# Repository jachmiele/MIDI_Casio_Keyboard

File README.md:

# MIDI Casio Keyboard
The goal of this project was to convert an old Casio keyboard into a MIDI controller.<br><br>
<h4>Requirements</h4>
MIDI.h library is required to run this code https://github.com/FortySevenEffects/arduino_midi_library/

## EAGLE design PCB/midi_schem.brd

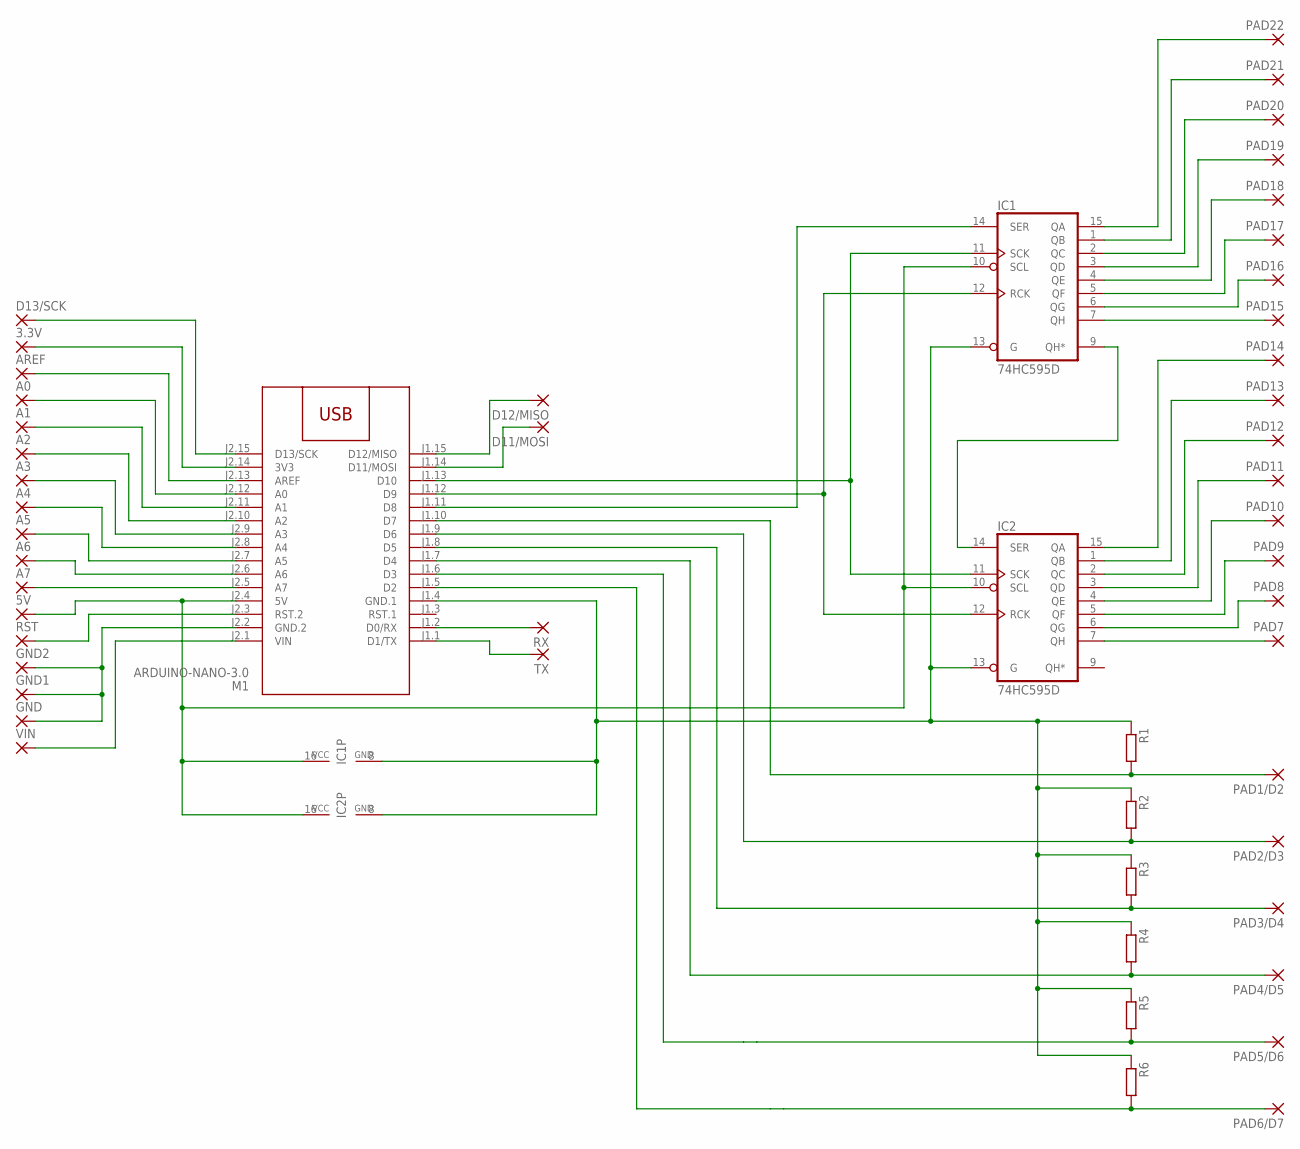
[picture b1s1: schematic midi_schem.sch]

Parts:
3.3V, 5V: 2,54/0,8
A0, A1, A2, A3, A4, A5, A6, A7: 2,54/0,8
AREF: 2,54/0,8
D11/MOSI, D12/MISO, D13/SCK: 2,54/0,8
GND, GND1, GND2: 2,54/0,8
IC1, IC2: 74HC595D; SO16
M1: ARDUINO-NANO-3.0
PAD1/D2, PAD2/D3, PAD3/D4, PAD4/D5, PAD5/D6, PAD6/D7, PAD7, PAD8, PAD9, PAD10, PAD11, PAD12, PAD13, PAD14, PAD15, PAD16, PAD17, PAD18, PAD19, PAD20, PAD21, PAD22: SMD2; SMD1,27-2,54
R1, R2, R3, R4, R5, R6: R-EU_0207/10; 0207/10
RST: 2,54/0,8
RX: 2,54/0,8
TX: 2,54/0,8
VIN: 2,54/0,8

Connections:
unnamed: IC1.14 (SER), M1.J1.11 (D8)
unnamed: 5V.1, IC1.10 (SCL), IC1.16 (VCC), IC2.10 (SCL), IC2.16 (VCC), M1.J2.4 (5V)
unnamed: IC1.8 (GND), IC1.13 (G), IC2.8 (GND), IC2.13 (G), M1.J1.4 (GND.1), R1.1, R2.1, R3.1, R4.1, R5.1, R6.1
unnamed: IC1.7 (QH), PAD15.1
unnamed: IC1.6 (QG), PAD16.1
unnamed: IC1.5 (QF), PAD17.1
unnamed: IC1.4 (QE), PAD18.1
unnamed: IC1.3 (QD), PAD19.1
unnamed: IC1.2 (QC), PAD20.1
unnamed: IC1.1 (QB), PAD21.1
unnamed: IC1.15 (QA), PAD22.1
unnamed: IC2.7 (QH), PAD7.1
unnamed: IC2.6 (QG), PAD8.1
unnamed: IC2.5 (QF), PAD9.1
unnamed: IC2.4 (QE), PAD10.1
unnamed: IC2.3 (QD), PAD11.1
unnamed: IC2.2 (QC), PAD12.1
unnamed: IC2.1 (QB), PAD13.1
unnamed: IC2.15 (QA), PAD14.1
unnamed: IC1.12 (RCK), IC2.12 (RCK), M1.J1.12 (D9)
unnamed: IC1.11 (SCK), IC2.11 (SCK), M1.J1.13 (D10)
unnamed: IC1.9 (QH*), IC2.14 (SER)
unnamed: A7.1, M1.J2.5 (A7)
unnamed: A6.1, M1.J2.6 (A6)
unnamed: A5.1, M1.J2.7 (A5)
unnamed: A4.1, M1.J2.8 (A4)
unnamed: A3.1, M1.J2.9 (A3)
unnamed: A2.1, M1.J2.10 (A2)
unnamed: A1.1, M1.J2.11 (A1)
unnamed: A0.1, M1.J2.12 (A0)
unnamed: AREF.1, M1.J2.13 (AREF)
unnamed: 3.3V.1, M1.J2.14 (3V3)
unnamed: D13/SCK.1, M1.J2.15 (D13/SCK)
unnamed: M1.J1.10 (D7), PAD1/D2.1, R1.2
unnamed: M1.J1.2 (D0/RX), RX.1
unnamed: M1.J1.1 (D1/TX), TX.1
unnamed: D11/MOSI.1, M1.J1.14 (D11/MOSI)
unnamed: D12/MISO.1, M1.J1.15 (D12/MISO)
unnamed: M1.J2.3 (RST.2), RST.1
unnamed: GND.1, GND1.1, GND2.1, M1.J2.2 (GND.2)
unnamed: M1.J2.1 (VIN), VIN.1
unnamed: M1.J1.9 (D6), PAD2/D3.1, R2.2
unnamed: M1.J1.8 (D5), PAD3/D4.1, R3.2
unnamed: M1.J1.7 (D4), PAD4/D5.1, R4.2
unnamed: M1.J1.6 (D3), PAD5/D6.1, R5.2
unnamed: M1.J1.5 (D2), PAD6/D7.1, R6.2

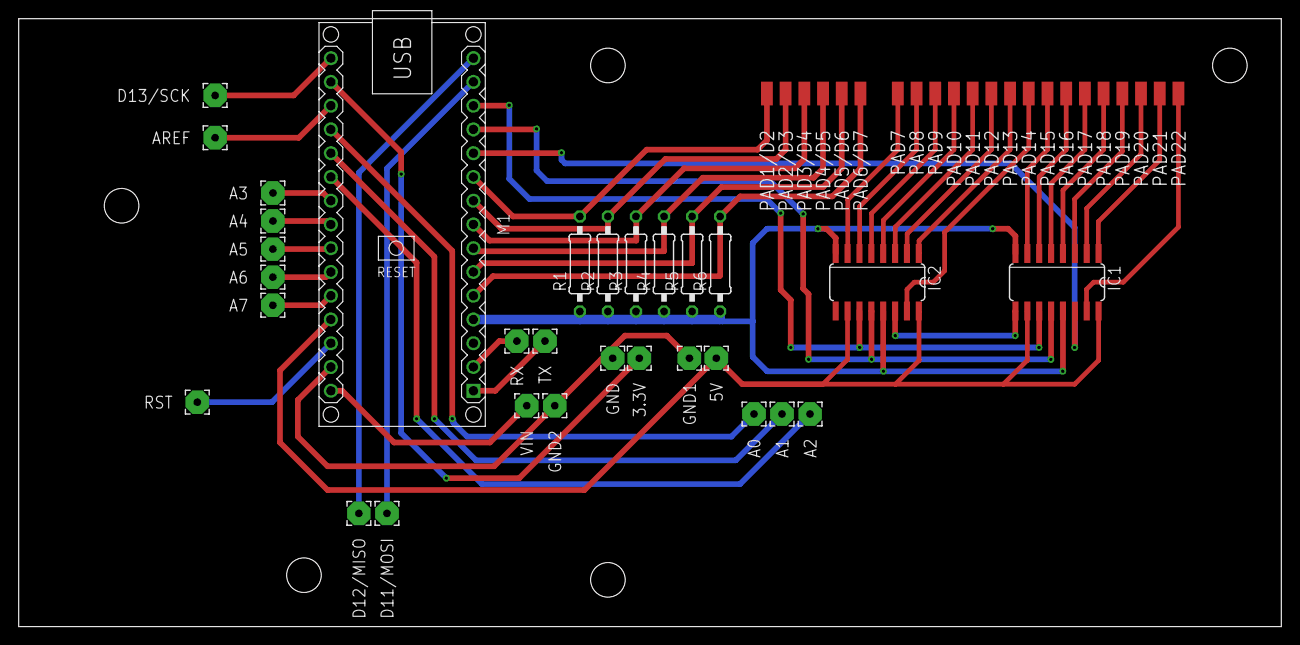
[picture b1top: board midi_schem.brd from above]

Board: 2 copper layers, 135.0 x 65.0 mm, 52 parts (0 on the bottom side), 46 nets.

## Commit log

2021-06-14 Set theme jekyll-theme-tactile

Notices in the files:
parts and their libraries:
diy-modules: Released under the Creative Commons Attribution 4.0 International License: http://creativecommons.org/licenses/by/4.0
